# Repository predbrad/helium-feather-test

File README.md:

<!-- HTML Comment -->

<!-- GitHub Markdown / HTML Format Tips

* Line Breaks in Text
  <br/> for single break

* Link with spaces in file path
  [Link Text](/folder/file%20path%20with%20spaces)

* Link to a Heading
  [Link Text](#link-to-a-multi-word-heading)

* File paths must use forward slashes '/' to create useable relative links in GitHub

* Side-by-side images on GitHub

* Clickable Image URL link must have HTML code on SAME LINE, for example:

* Code Block Syntax Highlighting tags:
  http://www.rubycoloredglasses.com/2013/04/languages-supported-by-github-flavored-markdown/
  ```cpp

* Emojis: copy-paste directly into text https://emojipedia.org/

* Table Generator: https://www.tablesgenerator.com/markdown_tables
  | header A | header B | header C |
  |----------|----------|----------|
  | item 1   | item 2   | item 3   |
  |          |          |          |
-->

<!-- Project Title -->
#  Helium Feather Test

<!-- Project Description -->
Connect to the helium network... or bust.

---

### README Outline
* [**Documentation**](#documentation)
    * [User Documentation](#user-documentation)
    * [Developer Documentation](#developer-documentation)

<!--    * [System Block Diagram](#system-block-diagram) -->
<!--    * [Developer Resources](#developer-resources)-->
<!--    * [Production Documentation](#production-documentation)-->
* [**Hardware**](#hardware)
* [**Firmware**](#firmware)
* [**Software**](#software)
 ---

##  Documentation

<!--
### System Block Diagram
  <br><br>
-->

###  User Documentation
*  [**Command Line Interface Guide**](docs/command_line_interface_guide.md)
<!--
1. Initial Setup User Guide
1. Quick Start User Guide
1. Field User Guide
1. Technical User Manual
-->

1. [Initial Setup (from Helium)](https://github.com/helium/devdocs/blob/21bee22ed5c32c6a67d74756c32bfa0053543666/devices/arduino-quickstart/adafruit-feather-m0-rfm95.md)
1. REMINDER: Add jumper from io1 and 6, also paste in the correct keys

### Developer Documentation

*  [**Firmware File Structure**](docs/firmware_file_structure.md)

*  [**Project Folder Structure**](/utils/print_folder_structure/folder_structure.md)
    > _**Note**_: to update, run [`print_folder_structure.bat`](/utils/print_folder_structure) from the locally cloned repo on a _Windows 10_ PC

<!-- 1. [**Example Firmware Setup Guide** ](docs/example_firmware_setup_guide.md) -->

<!--
### Developer Resources
-->

<!--
#### Production Documentation
1. Firmware Upload Procedure
1. Device Commissioning & Configuration Procedure
1. Production & Assembly Guide
1. Functional Verification Procedure
-->

---

##  Hardware

**Where to buy**: [Adafruit Feather M0 Radio with LoRa Radio Module](https://learn.adafruit.com/adafruit-feather-m0-radio-with-lora-radio-module/using-the-rfm-9x-radio) <!-- | [Simplified PDF](docs/bom-simplified.pdf)-->

<!--**Photo Gallery**-->

<!--
#### Electronics

* **Schematic**: [PDF](docs/schematic.pdf) <br>

<br><br>
* **PCB Design**: [Autodesk Eagle Files](hardware/elec/) <br>

-->

<!--
#### Mechanical
* **3D Design**: [eDrawings Files](hardware/mech/eDrawings) <br>

-->

---

##  Firmware

**Source Code**: [`project_name`](firmware/platformio_ide)

* **Target device**: [*Adafruit Feather M0 Radio with LoRa Radio Module*](https://learn.adafruit.com/adafruit-feather-m0-radio-with-lora-radio-module/using-the-rfm-9x-radio)

* **IDE**: [PlatformIO IDE](https://platformio.org/)
* **Libraries**: see `libraries` section in arduino_ide folder
<!--
  * **Protocol Stack**:
  * **Compiler Toolchain**:
-->

---

<!--
##  Software

---
-->

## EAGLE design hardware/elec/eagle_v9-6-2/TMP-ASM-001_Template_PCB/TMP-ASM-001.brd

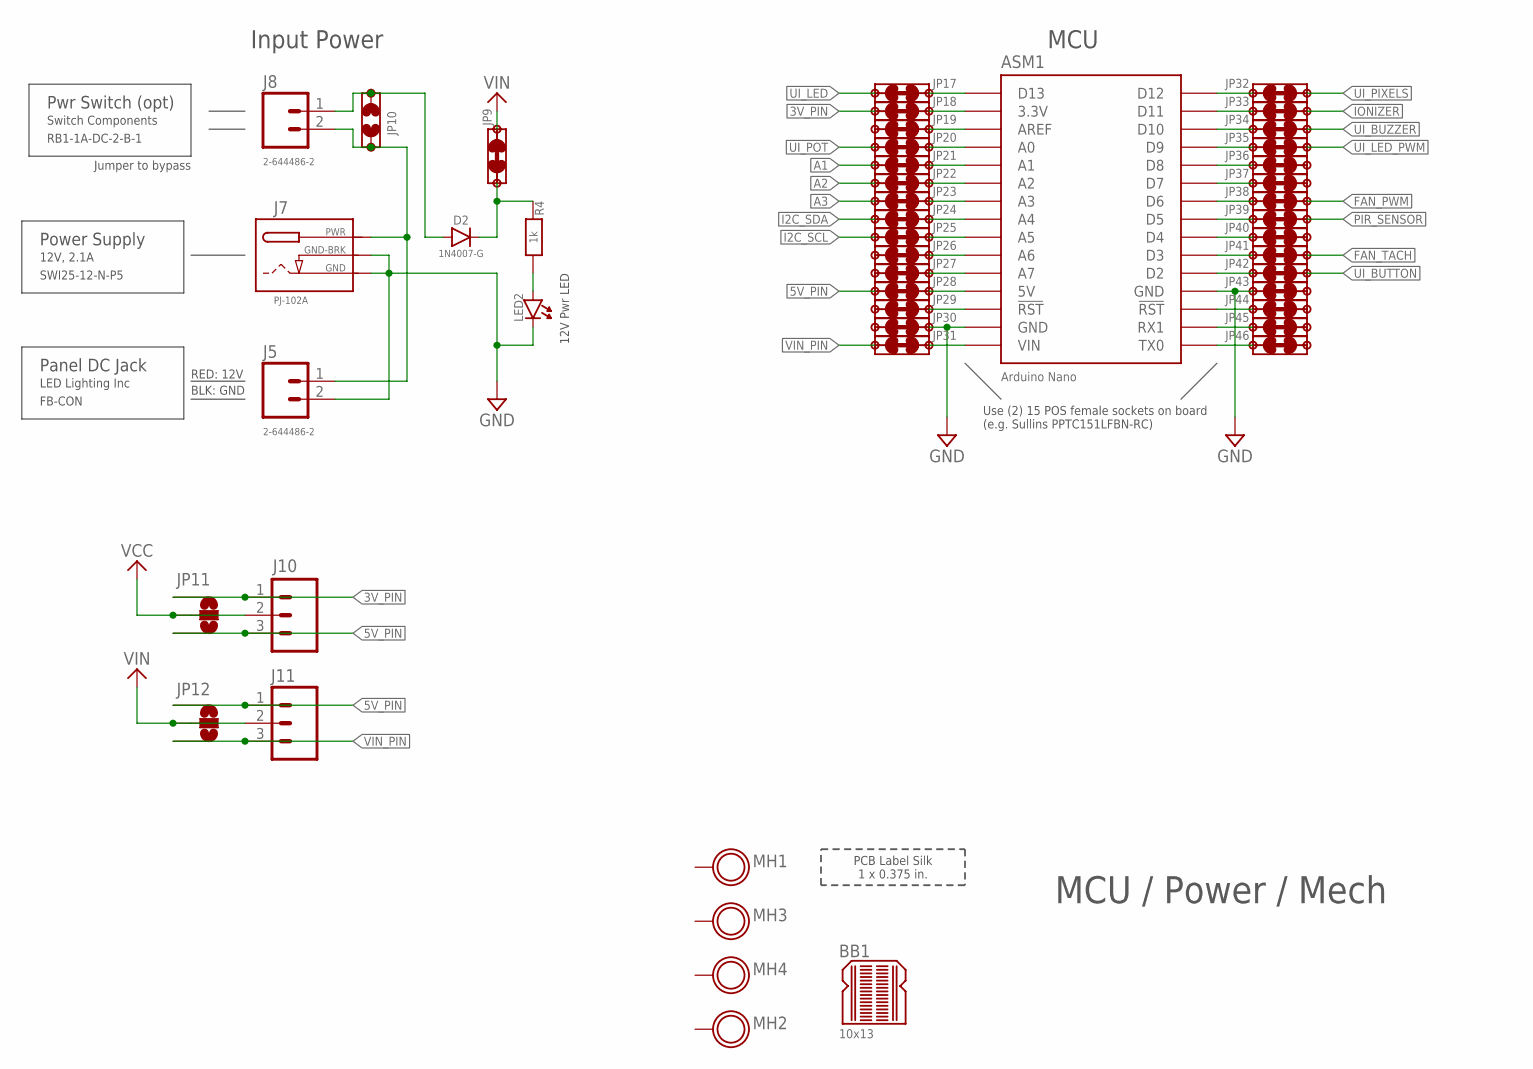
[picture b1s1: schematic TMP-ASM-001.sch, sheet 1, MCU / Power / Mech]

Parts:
ASM1: ASM_ARDUINO_NANO_NO-ICSP-LOCKING; ASM_ARDUINO_NANO_NO-ICSP_LOCKING
BB1: 10x13; BREADBOARD_PROTO_10X13
D2: 1N4007-G; DIODE-1N4007
J5, J8: 2-644486-2; TE_MTA-100_2POS-PTH-VERT
J7: PJ-102A; DCJACK_2MM-PIN,1MM-DRILL_THT_LOCKING
J10, J11: CON_HEADER_1X3LOCK; 1X03_LOCK
JP9, JP17, JP18, JP19, JP20, JP21, JP22, JP23, JP24, JP25, JP26, JP27, JP28, JP29, JP30, JP31, JP32, JP33, JP34, JP35, JP36, JP37, JP38, JP39, JP40, JP41, JP42, JP43, JP44, JP45, JP46: CON_JUMPER_PTH-2-NC-0.25W_RES_VERT_DRC-FRIENDLY; CON_JUMPER_NC_RES_VERT-0.4_DRC-FRIENDLY
JP10: CON_JUMPER_PTH-2-NO-DRC_FRIENDLY; CON_JUMPER_NO_RES_VERT-0.4_DRC-FRIENDLY
JP11, JP12: CON_JUMPER_PAD-3-ALL_NOFULL_BOX_SILK; PAD-JUMPER-3-NO_YES_SILK_FULL_BOX
LED2: LED_THT-3MM_LOCKING; LED3MM
MH1, MH2, MH3, MH4: PCB_MOUNTING-HOLE_PLATED-0.129-IN_#4_FREE-FIT; MOUNTING_HOLE_0.129-IN_#4_FREE-FIT_PLATED
R4: 1k; AXIAL-0.3_TIGHT
U$66: PCB_IMG_LABEL_SILK-1X0.375_IN; LABEL_SILK_1X0.375_IN

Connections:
3V_PIN: J10.1, JP11.1, JP18.P1
5V_PIN: J10.3, J11.1, JP11.3, JP12.1, JP28.P1
A1: JP21.P1; also elsewhere on the board
A2: JP22.P1; also elsewhere on the board
A3: JP23.P1; also elsewhere on the board
FAN_PWM: JP38.P1; also elsewhere on the board
FAN_TACH: JP41.P1; also elsewhere on the board
GND: ASM1.GND@14 (GND), ASM1.GND@19 (GND), J5.2, J7.2 (GND), J7.3 (GND-BRK), JP30.P2, JP43.P2, LED2.CAT (C); also elsewhere on the board
I2C_SCL: JP25.P1; also elsewhere on the board
I2C_SDA: JP24.P1; also elsewhere on the board
IONIZER: JP33.P1; also elsewhere on the board
unnamed: ASM1.D12, JP32.P2
unnamed: ASM1.D11, JP33.P2
unnamed: ASM1.D10, JP34.P2
unnamed: ASM1.D9, JP35.P2
unnamed: LED2.AN (A), R4.P$1 (P1)
unnamed: ASM1.D8, JP36.P2
unnamed: ASM1.D7, JP37.P2
unnamed: ASM1.D6, JP38.P2
unnamed: ASM1.D5, JP39.P2
unnamed: ASM1.D4, JP40.P2
unnamed: ASM1.D3, JP41.P2
unnamed: ASM1.D2, JP42.P2
unnamed: ASM1.RST@18 (!RST!), JP44.P2
unnamed: ASM1.RX1, JP45.P2
unnamed: ASM1.TX0, JP46.P2
unnamed: ASM1.D13, JP17.P2
unnamed: J5.1, J7.1 (PWR), J8.2, JP10.P1
unnamed: D2.A, J8.1, JP10.P2
unnamed: ASM1.3.3V, JP18.P2
unnamed: ASM1.AREF, JP19.P2
unnamed: ASM1.A0, JP20.P2
unnamed: ASM1.A1, JP21.P2
unnamed: ASM1.A2, JP22.P2
unnamed: ASM1.A3, JP23.P2
unnamed: ASM1.A4, JP24.P2
unnamed: ASM1.A5, JP25.P2
unnamed: ASM1.A6, JP26.P2
unnamed: ASM1.A7, JP27.P2
unnamed: ASM1.5V, JP28.P2
unnamed: ASM1.RST@13 (!RST!), JP29.P2
unnamed: ASM1.VIN, JP31.P2
unnamed: D2.C, JP9.P1, R4.P$2 (P2)
PIR_SENSOR: JP39.P1; also elsewhere on the board
UI_BUTTON: JP42.P1; also elsewhere on the board
UI_BUZZER: JP34.P1; also elsewhere on the board
UI_LED: JP17.P1; also elsewhere on the board
UI_LED_PWM: JP35.P1; also elsewhere on the board
UI_PIXELS: JP32.P1; also elsewhere on the board
UI_POT: JP20.P1; also elsewhere on the board
VCC: J10.2, JP11.2; also elsewhere on the board
VIN: J11.2, JP9.P2, JP12.2; also elsewhere on the board
VIN_PIN: J11.3, JP12.3, JP31.P1

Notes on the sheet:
Use (2) 15 POS female sockets on board (e.g. Sullins PPTC151LFBN-RC)
Pwr Switch (opt)
Switch Components
RB1-1A-DC-2-B-1
Jumper to bypass
Power Supply
12V, 2.1A
SWI25-12-N-P5
MCU / Power / Mech
Input Power
MCU
Panel DC Jack
LED Lighting Inc
FB-CON
RED: 12V
BLK: GND
12V Pwr LED

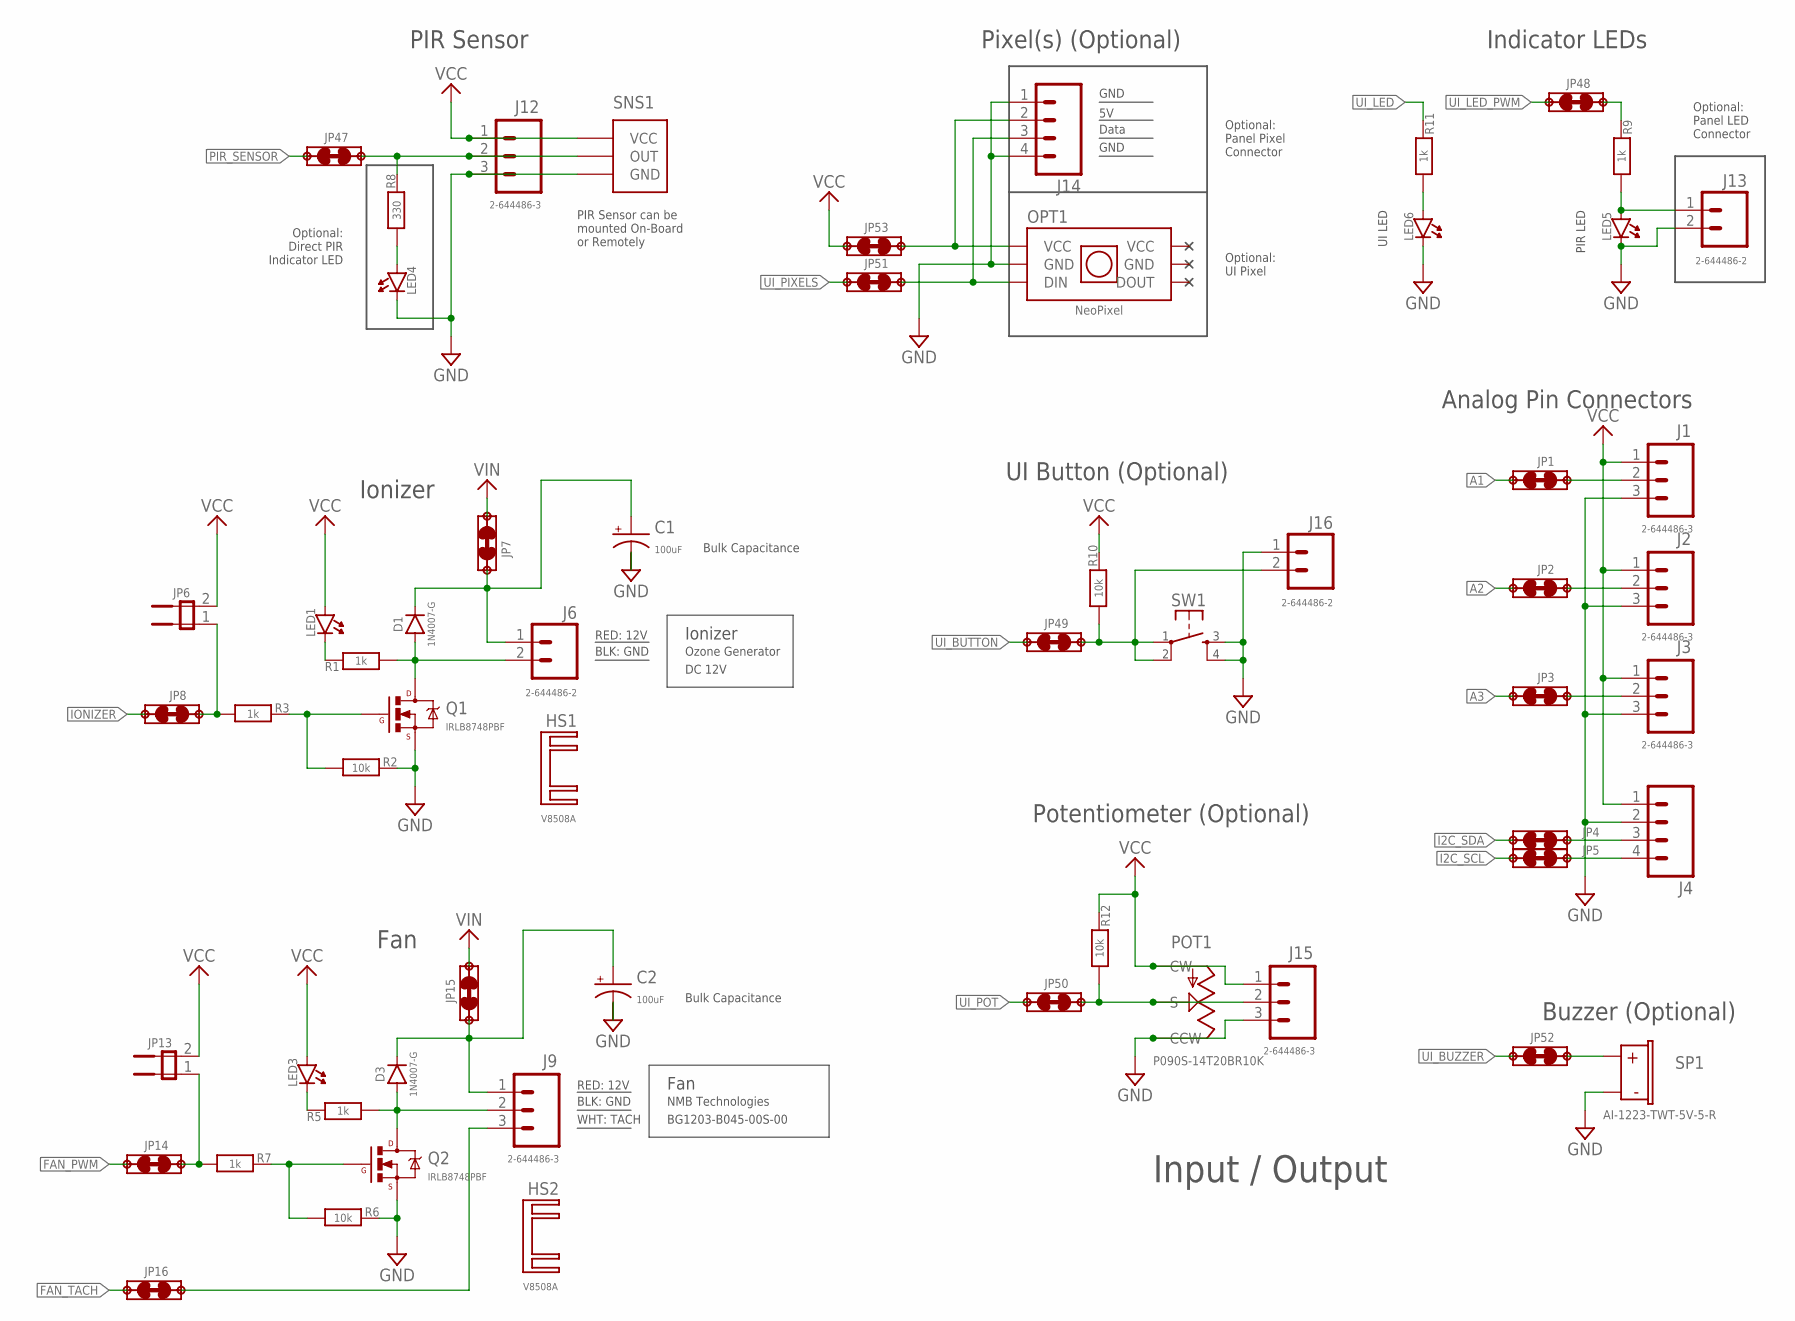
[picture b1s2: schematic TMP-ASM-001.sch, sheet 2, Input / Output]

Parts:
C1, C2: 100uF; CAP-E_8MM-DIA_X_3MM-LEAD
D1, D3: 1N4007-G; DIODE-1N4007
HS1, HS2: V8508A; HEATSINK_V8508
J1, J2, J3, J9, J12, J15: 2-644486-3; TE_MTA-100_3POS-PTH-VERT
J4, J14: CON_HEADER_1X4-TE_MTA-100_PTH_SHROUDED; TE_MTA-100_4POS-PTH-VERT
J6, J13, J16: 2-644486-2; TE_MTA-100_2POS-PTH-VERT
JP1, JP2, JP3, JP4, JP5, JP7, JP8, JP14, JP15, JP16, JP47, JP48, JP49, JP50, JP51, JP52, JP53: CON_JUMPER_PTH-2-NC-0.25W_RES_VERT_DRC-FRIENDLY; CON_JUMPER_NC_RES_VERT-0.4_DRC-FRIENDLY
JP6, JP13: CON_JUMPER_PIN_1X2-LOCKING; 1X02_LOCK
LED1, LED3, LED4, LED5, LED6: LED_THT-3MM_LOCKING; LED3MM
OPT1: OPT_WS2812_ASM_ADAFRUIT_THT; WS2812_ASM_ADAFRUIT_THT
POT1: P090S-14T20BR10K; POT-TT_P090S
Q1, Q2: IRLB8748PBF; TO-220-VERTICAL-LOCKING
R1, R3, R5, R7, R9, R11: 1k; AXIAL-0.3_TIGHT
R2, R6, R10, R12: 10k; AXIAL-0.3_TIGHT
R8: 330; AXIAL-0.3_TIGHT
SNS1: ASM_PIR_MOTION_SENSOR
SP1: AI-1223-TWT-5V-5-R; BUZZER-2PIN-12MM-D
SW1: EMD_SWITCH_SPST_MOM_THT-TL1100X_12MMX12MM; TL1100X

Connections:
A1: JP1.P2; also elsewhere on the board
A2: JP2.P2; also elsewhere on the board
A3: JP3.P2; also elsewhere on the board
FAN_PWM: JP14.P2; also elsewhere on the board
FAN_TACH: JP16.P2; also elsewhere on the board
GND: C1.-, C2.-, J1.3, J2.3, J3.3, J4.2, J12.3, J13.2, J14.1, J14.4, J15.3, J16.1, LED4.CAT (C), LED5.CAT (C), LED6.CAT (C), OPT1.P$2 (GND), OPT1.P$5 (GND), POT1.3 (CCW), Q1.3 (S), Q2.3 (S), R2.P$2 (P2), R6.P$2 (P2), SNS1.GND, SP1.-, SW1.3 (3B), SW1.4 (4B); also elsewhere on the board
I2C_SCL: JP5.P2; also elsewhere on the board
I2C_SDA: JP4.P2; also elsewhere on the board
IONIZER: JP8.P2; also elsewhere on the board
unnamed: LED4.AN (A), R8.P$1 (P1)
unnamed: LED3.CAT (C), R5.P$2 (P2)
unnamed: LED1.CAT (C), R1.P$2 (P2)
unnamed: C1.+, D1.C, J6.1, JP7.P1
unnamed: LED6.AN (A), R11.P$1 (P1)
unnamed: J9.3, JP16.P1
unnamed: D3.A, J9.2, Q2.2 (D), R5.P$1 (P1)
unnamed: Q2.1 (G), R6.P$1 (P1), R7.P$2 (P2)
unnamed: J12.2, JP47.P1, R8.P$2 (P2), SNS1.OUT
unnamed: J13.1, LED5.AN (A), R9.P$1 (P1)
unnamed: JP6.1, JP8.P1, R3.P$1 (P1)
unnamed: C2.+, D3.C, J9.1, JP15.P2
unnamed: JP13.1, JP14.P1, R7.P$1 (P1)
unnamed: JP52.P1, SP1.+
unnamed: D1.A, J6.2, Q1.2 (D), R1.P$1 (P1)
unnamed: J16.2, JP49.P1, R10.P$1 (P1), SW1.1 (1A), SW1.2 (2A)
unnamed: J14.3, JP51.P1, OPT1.P$3 (DIN)
unnamed: JP48.P1, R9.P$2 (P2)
unnamed: Q1.1 (G), R2.P$1 (P1), R3.P$2 (P2)
unnamed: J4.3, JP4.P1
unnamed: J4.4, JP5.P1
unnamed: J1.2, JP1.P1
unnamed: J2.2, JP2.P1
unnamed: J3.2, JP3.P1
unnamed: J15.2, JP50.P1, POT1.2 (S), R12.P$1 (P1)
unnamed: J14.2, JP53.P1, OPT1.P$1 (VCC)
PIR_SENSOR: JP47.P2; also elsewhere on the board
UI_BUTTON: JP49.P2; also elsewhere on the board
UI_BUZZER: JP52.P2; also elsewhere on the board
UI_LED: R11.P$2 (P2); also elsewhere on the board
UI_LED_PWM: JP48.P2; also elsewhere on the board
UI_PIXELS: JP51.P2; also elsewhere on the board
UI_POT: JP50.P2; also elsewhere on the board
VCC: J1.1, J2.1, J3.1, J4.1, J12.1, J15.1, JP6.2, JP13.2, JP53.P2, LED1.AN (A), LED3.AN (A), OPT1.P$6 (VCC), POT1.1 (CW), R10.P$2 (P2), R12.P$2 (P2), SNS1.VCC; also elsewhere on the board
VIN: JP7.P2, JP15.P1; also elsewhere on the board

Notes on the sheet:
Ionizer
Ozone Generator
DC 12V
RED: 12V
BLK: GND
Fan
NMB Technologies
BG1203-B045-00S-00
WHT: TACH
Optional: Direct PIR Indicator LED
PIR Sensor can be mounted On-Board or Remotely
UI LED
PIR LED
UI Button (Optional)
Buzzer (Optional)
PIR Sensor
Potentiometer (Optional)
Indicator LEDs
Optional: Panel LED Connector
Optional: Panel Pixel Connector
GND
Data
Pixel(s) (Optional)
Optional: UI Pixel
Input / Output
Bulk Capacitance
Analog Pin Connectors

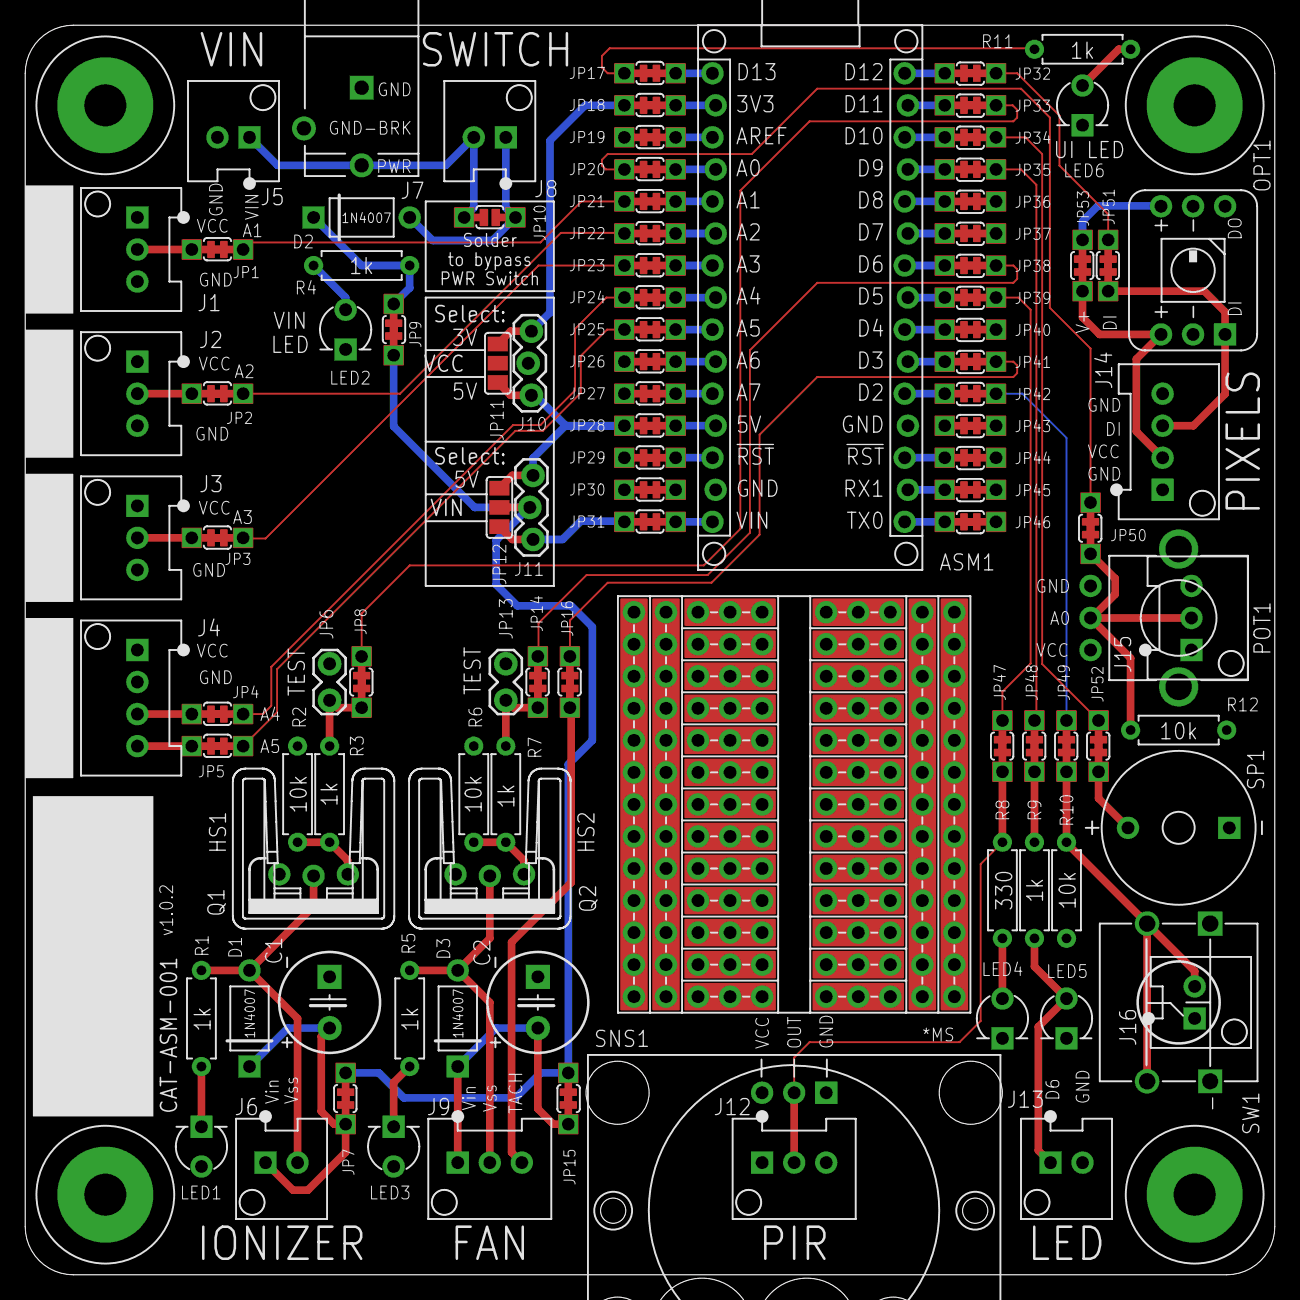
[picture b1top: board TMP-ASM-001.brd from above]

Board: 2 copper layers, 99.1 x 99.1 mm, 108 parts (0 on the bottom side), 79 nets.

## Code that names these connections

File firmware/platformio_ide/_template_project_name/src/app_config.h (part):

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    #define PIN_FADE_LED                       9  // PWM        //
    //#define PIN_                             8  //            // not on Feather
    //#define PIN_                             7  //            // not on Feather
    #define PIN_FAN_PWM                        6  // PWM        //
    //#define PIN_                             5  // PWM        //
    //#define PIN_                             4  //            // not on Feather
    #define PIN_FAN_TACH                       3  // INT1; PWM  //
    #define PIN_UI_BUTTON                      2  // INT0       //
    //#define PIN_                             0  // RX0 (avoid use) //
    //#define PIN_                             1  // TX1        //

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
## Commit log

2021-05-08 setting up board and libraries
2021-05-21 * minor README update. Testing git sync setup...
2021-06-04 working example ex device keys
2021-06-04 readme notes
